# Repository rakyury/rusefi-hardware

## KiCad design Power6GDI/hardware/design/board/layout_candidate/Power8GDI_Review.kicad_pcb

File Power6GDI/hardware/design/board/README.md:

# Review PCB builder

**Incomplete engineering PCB. Do not fabricate, energize or claim qualification.**
The original placeholder PCB is untouched. This folder builds real footprints,
pad nets and routed subdomains from the current electrical hierarchy.

Use the pinned official `kicad/kicad:9.0` image, KiCad9.0.9; digest is recorded
in `source_provenance.json`. No network is needed during generation. Mount the
repository at`/src`, set working directory`/src`, and run:

```text
python3 Power6GDI/hardware/design/board/build_connector_schematic.py
kicad-cli sch export netlist --format kicadxml -o Power6GDI/hardware/design/board/connectors.xml Power6GDI/hardware/design/board/connectors.kicad_sch
python3 Power6GDI/hardware/design/board/build_board.py
python3 Power6GDI/hardware/design/board/verify_board.py Power6GDI/hardware/design/board/review/Power8GDI_Review.kicad_pcb Power6GDI/hardware/design/core.net
kicad-cli pcb drc --format json --all-track-errors --severity-all --exit-code-violations -o Power6GDI/hardware/design/board/review/drc.json Power6GDI/hardware/design/board/review/Power8GDI_Review.kicad_pcb
```

The authoritative integrated root XML is `design/core.net`. It includes
J601..604, so the current verifier uses only this XML. Duplicate refs
and conflicting pad assignments are errors. Before root integration the
builder also accepts whole separate GDI/power XML sheets; a partially duplicate
hierarchy is rejected. `--design-root`, `--source-board`, `--pinout` and
`--output-dir` support isolated build snapshots without editing source designs.

Source electrical flags includingDNP and BOM exclusion are carried to the
physical board and independently compared on reload. A source off-board
component fails instead of silently becoming a physical pad.

The copper transfer uses KiCad's actual source connectivity graph, exact
oldref→newref mapping and sourcepad→targetnet mapping. It rejects any source
net that would join two distinct target nets. Branches terminating at removed
logic/connectors and open physical endpoints are removed. Ground vias count
as real plane endpoints only with a retained pad. Groundplane fill and DRC are
run on the resulting board. Reference power/sense-zone shapes remain visible;
source clearances are **not** automatically accepted as new design rules.

The stageB reference3V3/5V supply buses cross the provisional edge when rotated;
they are explicitly omitted for rerouting to the new regulators. Remaining
unrouted connections are reported, not represented by invented tracks.

The provisional outline245×165mm,4-layer1.6mm stackup and clearances are design
inputs, not a manufacturer's approved stackup. Outer copper70µm, inner35µm,
dielectrics120/1130/120µm, soldermask10µm each side are an engineering proposal.
Current, thermal, impedance, transient, dielectric and assembly budgets remain
open. PCB pads/trace exports alone do not demonstrate electrical qualification.

The outline, donor stage frames, connector/MCU/ignition anchors and functional
regions come from `layout_profiles/<name>.json` (`--layout-profile`, default
`layout_profiles/245x165.json`). `compare_boards.py A B` proves two builds are
geometrically identical. `ground_stitch.py <board>` adds guarded GND vias for
islands on a saved, filled candidate (one per island; refused where copper,
holes, mask or the edge leave no room). See `docs/PCB_LAYOUT_PROFILE_2026_11_05.md`.
`review_autoroute.py <placement> <autorouted> <out>` measures the machine copper
of an autorouted candidate block by block (layers incl. In1, widths against the
project netclasses, the project clearance rule on every router item, sensitive
nets near switching copper, diff pairs, GND islands, remaining gap per block);
verdicts are written by hand in `docs/PCB_AUTOROUTE_REVIEW_2026_11_10.md`.

Run portable contract tests with:

```text
python -m unittest discover -s Power6GDI/hardware/design/board/tests -v
```

`render_preview.py` optionally converts actual KiCad SVG plots toPNG using
PyQt6/QtSvg. It does not infer or invent copper. Rendered exports and full DRC
reports belong in the chosen build/output directory; no manufacturing Gerber
release is produced while the DRC and functional gates fail.

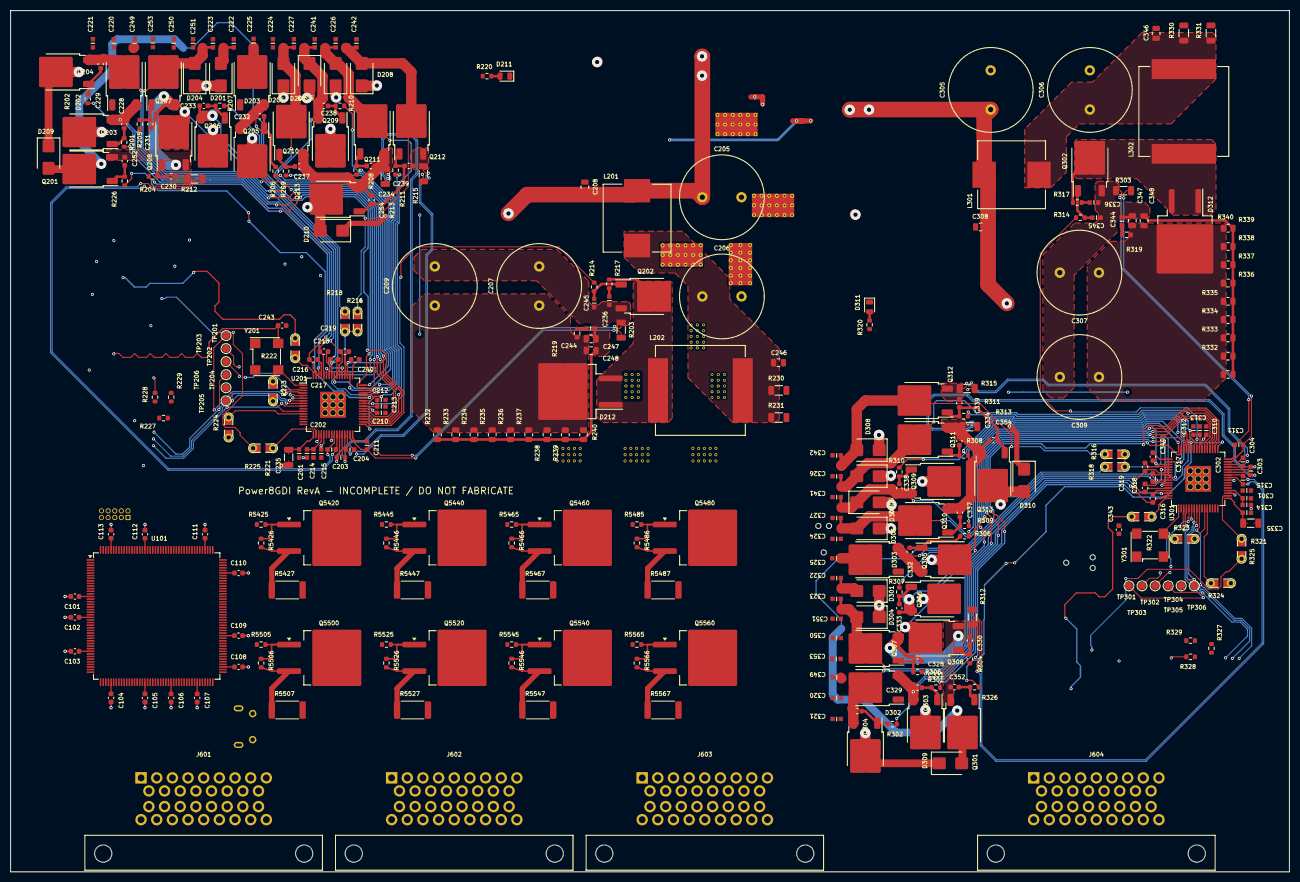
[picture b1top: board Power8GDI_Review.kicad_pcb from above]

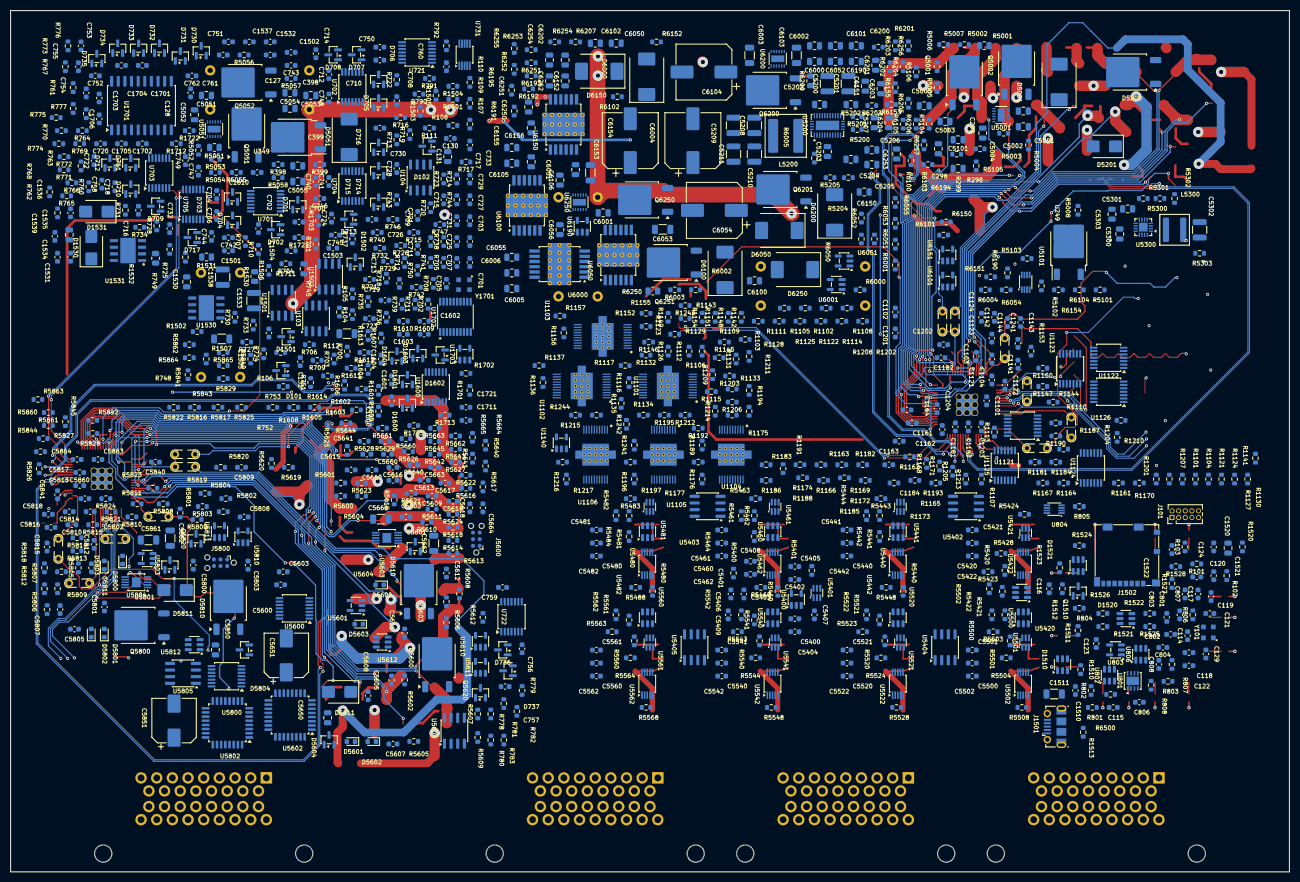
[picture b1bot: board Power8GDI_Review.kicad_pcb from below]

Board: 4 copper layers, 245.0 x 165.0 mm, 1262 parts (954 on the bottom side), 760 nets.

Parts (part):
C101, C102, C103, C104, C105, C106, C107, C108, C109, C110, C111, C112, C113, C117, C119, C121, C123, C124, C127, C128, C740, C742, C744, C746, C748, C758, C759, C761, C1101, C1102, C1103, C1121, C1122, C1123, C1141, C1142, C1143, C1161, C1162, C1163, C1181, C1182, C1183, C1201, C1202, C1203, C1241, C1501, C1502, C1510, C1520, C1532, C1537, C1610, C5640, C5641, C5660, C5663, C5664, C5840, C5841, C5860, C5863, C5864: 100n 16V X7R; C_0603_1608Metric
C114: 4.7u 16V X7R; C_0603_1608Metric
C115, C116: 2.2u 10V X7R; C_0603_1608Metric
C118, C120, C122, C741, C743, C745, C747, C749, C762, C1104, C1124, C1144, C1164, C1184, C1204: 1u 16V X7R; C_0603_1608Metric
C129, C701, C703, C705, C707, C709, C711, C713, C715, C717, C719, C721, C723, C725, C727, C729, C731, C733: 10n 16V X7R; C_0603_1608Metric
C130, C1503, C1531, C1534, C1536, C1539: 100n 50V X7R; C_0603_1608Metric
C131, C1504, C1530, C1535: 1u 50V X7R; C_0805_2012Metric
C132, C760, C1505: 1n 100V C0G; C_0603_1608Metric
C201, C301: 1u; REF_C9
C202, C302: 330p; REF_C10
C203, C303: 330p; REF_C11
C204, C304: 330p; REF_C13
C205, C305: 1200uF; REF_C14
C206, C306: 1200uF; REF_C15
C207, C307: 470uF; REF_C16
C208, C308: 0.22uF; REF_C17
C209, C309: 470uF; REF_C21
C210, C310: 100n; REF_C23
C211, C311: 330p; REF_C24
C212, C312: 4.7u; REF_C26
C213, C313: 100n; REF_C28
C214, C314: 100n; REF_C32
C215, C315: 100n; REF_C34
C216, C316: 0.33uF; REF_C39
C217, C317: 0.33uF; REF_C40
C218, C318: 0.33uF; REF_C41
C219, C319: 0.33uF; REF_C42
C220, C320: 4700p; REF_C43
C221, C321: 4700p; REF_C44
C222, C322: 4700p; REF_C45
C223, C323: 4700p; REF_C46
C224, C324: 4700p; REF_C47
C225, C325: 4700p; REF_C48
C226, C326: 4700p; REF_C49
C227, C327: 4700p; REF_C50
C228, C328: 1000pF; REF_C52
C229, C329: 1000pF; REF_C53
C230, C330: 1000pF; REF_C54
C231, C331: 1000pF; REF_C55
C232, C332: 1000pF; REF_C56
C233, C333: 1000pF; REF_C57
C234, C334: 1000pF; REF_C58
C235, C335: 100n; REF_C59
C236, C336: 330p; REF_C60
C237, C337: 1000pF; REF_C61
C238, C338: 1000pF; REF_C62
C239, C339: 1000pF; REF_C63
C240, C340: 0.33uF; REF_C64
C241, C341: 4700p; REF_C65
C242, C342: 4700p; REF_C67
C243, C343: 1000pF; REF_C71
C244, C344: 330p; REF_C73
C245, C345: 470p; REF_C74
C246, C346: 0.22uF; REF_C80
C247, C347: 0.22uF; REF_C81
C248, C348: 0.22uF; REF_C82
C249, C349: 4700p; REF_C84
C250, C350: 4700p; REF_C85
C251, C351: 4700p; REF_C86
C252, C352: 1000pF; REF_C87
C253, C353: 4700p; REF_C88
C254, C354: 1000pF; REF_C89
C298, C398: 330n 50V X7R; REF_C17
C299, C399: 100n 25V X7R; REF_C17
C700, C702, C704, C706, C708, C710, C712, C714, C716, C718, C720, C722, C724, C726, C728, C730, C732: 1n 50V C0G; C_0603_1608Metric
C750, C751, C752, C753, C754, C755, C756, C757, C1600, C1601, C1602, C1603, C1604: 47p 100V C0G; C_0603_1608Metric
C801, C802, C803, C804, C807, C1702, C1703, C1704, C1705, C1706: 100nF 25V X7R; C_0603_1608Metric
C806: 120pF 50V C0G 1%; C_0603_1608Metric
C808: 1nF 50V C0G 5%; C_0603_1608Metric
C1511: 1n 2kV C0G; C_1206_3216Metric
C1521: 10u 16V X7R; C_0805_2012Metric
C1522: 1n 16V X7R; C_0603_1608Metric
C1533, C1538: 22u 50V X7R; C_1210_3225Metric
C1701: 4.7uF 16V X7R; C_0603_1608Metric
C1711, C1721: 3.3nF 50V C0G; C_0603_1608Metric
C5001, C5003, C5051, C5053, C5650, C5850, C6200, C6202, C6250, C6252: 100n 100V X7R; C_0805_2012Metric
C5002, C5052, C5101, C5301, C6000, C6001, C6050, C6051, C6100, C6101, C6150, C6151, C6190, C6201, C6251: 100n 25V X7R; C_0805_2012Metric
C5004, C5054, C6002, C6052, C6102, C6152, C6203, C6253: 100n 50V X7R; C_0805_2012Metric
C5005, C5055, C6204, C6254: 22n 100V X7R; C_0805_2012Metric
C5200, C5201: 10u 100V X7R; C_1210_3225Metric
C5202: 47n 100V X7R; C_0805_2012Metric
C5203: 470n 25V X7R; C_0805_2012Metric
C5204: 2.2u 16V X7R; C_0805_2012Metric
C5205: 1u 16V X7R; C_0805_2012Metric
C5206: 22n 16V X7R; C_0805_2012Metric
C5207: 180p 50V C0G; C_0805_2012Metric
C5208, C5209, C5210, C5211: 47u 25V X7R; C_1210_3225Metric
C5300: 10u 25V X7R; C_0805_2012Metric
C5302: 22u 16V X7R; C_1210_3225Metric
C5303: 3.3n 25V C0G; C_0805_2012Metric
C5400, C5401, C5402, C5404, C5406, C5408, C5420, C5421, C5422, C5440, C5441, C5442, C5460, C5461, C5462, C5480, C5481, C5482, C5500, C5501, C5502, C5520, C5521, C5522, C5540, C5541, C5542, C5560, C5561, C5562: 100n 25V X7R; C_0603_1608Metric
C5403, C5405, C5407, C5409: 1u 25V X7R; C_0603_1608Metric
C5600, C5607, C5609, C5610, C5611, C5800, C5807, C5809, C5810, C5811: 1u; C_0603_1608Metric
C5601, C5602, C5605, C5608, C5612, C5613, C5614, C5615, C5617, C5618, C5801, C5802, C5805, C5808, C5812, C5813, C5814, C5815, C5817, C5818: 100n; C_0603_1608Metric
C5603, C5803: 33n; C_0603_1608Metric
C5616, C5816: 4.7u; C_0603_1608Metric
C5651, C5851: 47u 63V lowESR; CP_Elec_8x10
C5661, C5662, C5861, C5862: 10u 16V X7R effective>=4.7u; C_1206_3216Metric
C6003, C6053, C6103, C6153: 1u 50V X7R; C_1206_3216Metric
C6004, C6054, C6104, C6154: 100u 50V low ESR; CP_Elec_10x10.5
C6005, C6006, C6055, C6056, C6105, C6106, C6155, C6156: 1n 100V C0G; C_0805_2012Metric
D101, D1501: PESD2CAN; SOT-23
D102, D1502: BAS21,215; SOT-23
D201, D301: STPS2H100UY; REF_D9
D202, D302: SBR10200CTL; REF_D10
D203, D303: SBR10200CTL; REF_D11
D204, D304: STPS2H100UY; REF_D12
D205, D305: STPS2H100UY; REF_D13
D206, D306: STPS2H100UY; REF_D14
D207, D307: STPS2H100UY; REF_D15
D208, D308: STPS2H100UY; REF_D16
D209, D309: STPS2H100UY; REF_D17
D210, D310: STPS2H100UY; REF_D19
D211, D311: LED_Small; REF_D31
D212, D312: SDURB1020CT; REF_D34
D701, D702, D703, D704, D705, D706, D707, D708, D709, D710, D711, D712, D713, D714, D715, D716, D717, D730, D731, D732, D733, D734, D735, D736, D737, D1600, D1601, D1602, D1603, D1604: BAT54S,215; SOT-23
D1510, D1520, D1521: USBLC6-2SC6; SOT-23-6
D1530, D1531: STPS2H100UY; D_SMB
D5001, D5051, D6200, D6250: SMCJ33CA; D_SMC
D5200, D5610, D5810: STPS5H100BY-TR; TO-252-2
D5201, D5611, D5811: SMBJ24CA; D_SMB
D5600, D5603, D5800, D5803: LED-RED-0603; LED_0603_1608Metric
D5601, D5801: LED-GREEN-0603; LED_0603_1608Metric
D5602, D5802: LED-BLUE-0603; LED_0603_1608Metric
D5604, D5804: PESD1CAN; SOT-23
D6000, D6050, D6100, D6150: SMCJ18CA; D_SMC
J101: SWD 3V3 target reference; PinHeader_2x05_P1.27mm_Vertical
J601, J602, J603, J604: 6437288-1 / KEY1 CANDIDATE; TE_6437288-1_34way
J1501: Molex 1050170001; USB_Micro-B_Molex-105017-0001
J1502: Molex 1040310811; microSD_HC_Molex_104031-0811
J5600, J5800: Conn_02x03_Odd_Even; Tag-Connect_TC2030-IDC-NL_2x03_P1.27mm_Vertical
L201, L301: 6.8uH; REF_L1
L202, L302: 10uH; REF_L2
L5200: XAL7070-682MEC 6.8uH; L_Coilcraft_XAL7070-XXX
L5300: XAL5030-222MEC 2.2uH; L_Coilcraft_XAL5030-XXX
Q201, Q301: BUK9230-100B; REF_Q1
Q202, Q302: BUK9230-100B; REF_Q2
Q203, Q303: BUK9230-100B; REF_Q3
Q204, Q304: BUK9230-100B; REF_Q4
Q205, Q305: BUK9230-100B; REF_Q5
Q206, Q306: BUK9230-100B; REF_Q6
Q207, Q307: BUK9230-100B; REF_Q7
Q208, Q308: BUK9230-100B; REF_Q8
Q209, Q309: BUK9230-100B; REF_Q9
Q210, Q310: BUK9230-100B; REF_Q10
Q211, Q311: BUK9230-100B; REF_Q11
Q212, Q312: BUK9230-100B; REF_Q12
Q213, Q313: BUK9230-100B; REF_Q16
Q1510: 2N7002,215; SOT-23
Q5001, Q5002, Q5051, Q5052, Q6200, Q6201, Q6250, Q6251: IPD90N10S4-06; TO-252-2
Q5420, Q5440, Q5460, Q5480, Q5500, Q5520, Q5540, Q5560: STGB18N40LZT4; TO-263-2
Q5600, Q5800: VND7NV04TR-E; TO-252-2
Q5620, Q5820: BC847B-QR; SOT-23
R101, R111, R1506, R1520, R1713, R1723, R5644, R5844, R6500: 0R; R_0603_1608Metric
R102, R103, R104, R108, R110, R760, R763, R766, R769, R772, R775, R778, R781, R792, R1103, R1106, R1109, R1112, R1114, R1117, R1123, R1126, R1129, R1132, R1134, R1137, R1143, R1146, R1149, R1152, R1154, R1157, R1163, R1166, R1169, R1172, R1174, R1177, R1183, R1186, R1189, R1192, R1194, R1197, R1203, R1206, R1209, R1212, R1214, R1217, R1501, R1504, R1505, R1512, R1600, R1603, R1606, R1609, R1612, R5426, R5446, R5466, R5486, R5506, R5526, R5546, R5566, R5604, R5605, R5613, R5614, R5618, R5619, R5625, R5640, R5641, R5643, R5662, R5804, R5805, R5813, R5814, R5818, R5819, R5825, R5840, R5841, R5843, R5862, R6002, R6003, R6004, R6005, R6052, R6053, R6054, R6055, R6102, R6103, R6104, R6105, R6152, R6153, R6154, R6155, R6193, R6194, R6203, R6207, R6253, R6257: 10k; R_0603_1608Metric
R105, R109, R1513: 0R DNP; R_0603_1608Metric
R106, R1502, R5629, R5829: 120R DNP; R_0603_1608Metric
R107, R1503: 4.7k; R_0603_1608Metric
R112, R1507: 1k 1% 0.5W; R_1206_3216Metric
R201, R301: 10; REF_R10
R202, R302: 10; REF_R11
R203, R303: 0.01; REF_R12
R204, R304: 10; REF_R13
R205, R305: 10; REF_R14
R206, R306: 10; REF_R15
R207, R307: 10; REF_R16
R208, R308: 10; REF_R17
R209, R309: 10; REF_R18
R210, R310: 10; REF_R19
R211, R311: 10; REF_R20
R212, R312: 0.01; REF_R21
R213, R313: 0.01; REF_R22
R214, R314: 10; REF_R24
R215, R315: 0.01; REF_R26
R216, R316: Jumper-Pad-Pad; REF_R37
R217, R317: 220; REF_R38
R218, R318: DNP; REF_R41
R219, R319: 5.1; REF_R42
R220, R320: 75K; REF_R43
R221, R321: 0.01; REF_R45
R222, R322: DNP; REF_R80
R223, R323: DNP; REF_R81
R224, R324: DNP; REF_R82
R225, R325: DNP; REF_R83
R226, R326: 10; REF_R94
R227, R327: 1K; REF_R123
R228, R328: 1K; REF_R124
R229, R329: 1K; REF_R125
R230, R330: 2K; REF_R126
R231, R331: 2K; REF_R127
R232, R332: 56k; REF_R128
R233, R333: 56k; REF_R129
R234, R334: 56k; REF_R130
R235, R335: 56k; REF_R131
R236, R336: 56k; REF_R132
R237, R337: 56k; REF_R133
R238, R338: 56k; REF_R134
R239, R339: 56k; REF_R135
R240, R340: 56k; REF_R136
R298, R398: 910 1% minimum load; REF_R123
R299, R399: DNP_ENABLE_BOUNDARY; REF_R123
R700, R701, R703, R704, R706, R707, R709, R710, R712, R713, R715, R716, R718, R719, R721, R722, R724, R725, R727, R728, R730, R731, R733, R734, R736, R737, R739, R740, R742, R743, R745, R746, R748, R749, R5200, R5203, R5300: 100k 0.1%; R_0603_1608Metric
R702, R705, R708, R711, R714, R717, R720, R723, R726, R729, R732, R735, R738, R741, R744, R747, R750, R1510, R5401, R5600, R5601, R5616, R5617, R5622, R5626, R5627, R5628, R5800, R5801, R5816, R5817, R5822, R5826, R5827, R5828, R6202, R6206, R6252, R6256: 1k; R_0603_1608Metric
R751, R752, R753: 2.49k DNP; R_0603_1608Metric
R761, R764, R767, R770, R773, R776, R779, R782, R1523, R1524, R1525, R1526, R1527, R1528, R1601, R1604, R1607, R1610, R1613: 47k; R_0603_1608Metric
R762, R765, R768, R771, R774, R777, R780, R783, R1602, R1605, R1608, R1611, R1614: 10k DNP; R_0603_1608Metric
R790, R791, R5002, R5052, R6201, R6251: 10k 0.1%; R_0603_1608Metric
R801, R802, R803, R804, R805, R806, R1701, R1702, R5004, R5008, R5054, R5058, R5101, R5102, R5103, R5104, R5105, R5106, R5303, R5400, R5665, R5865: 10k 1%; R_0603_1608Metric
R807: 102k 0.1% 25ppm; R_0603_1608Metric
R808: 9.76k 0.1% 25ppm; R_0603_1608Metric
R1101, R1104, R1107, R1110, R1121, R1124, R1127, R1130, R1141, R1144, R1147, R1150, R1161, R1164, R1167, R1170, R1181, R1184, R1187, R1190, R1201, R1204, R1207, R1210, R1241, R1511, R5420, R5424, R5440, R5444, R5460, R5464, R5480, R5484, R5500, R5504, R5520, R5524, R5540, R5544, R5560, R5564, R5615, R5621, R5645, R5815, R5821, R5845, R6195: 100k; R_0603_1608Metric
R1102, R1105, R1108, R1111, R1115, R1116, R1122, R1125, R1128, R1131, R1135, R1136, R1142, R1145, R1148, R1151, R1155, R1156, R1162, R1165, R1168, R1171, R1175, R1176, R1182, R1185, R1188, R1191, R1195, R1196, R1202, R1205, R1208, R1211, R1215, R1216, R6000, R6001, R6050, R6051, R6100, R6101, R6150, R6151: 100R; R_0603_1608Metric
R1113, R1133, R1153, R1173, R1193, R1213, R6190, R6191, R6192: 47R; R_0603_1608Metric
R1242, R5003, R5007, R5053, R5057: 1k 1%; R_0603_1608Metric
R1243, R1244: 33R; R_0603_1608Metric
R1521, R1522: 22R; R_0603_1608Metric
R1530, R1531, R1532: 0R star return; R_0805_2012Metric
R1703, R1711, R1712, R1721, R1722, R5204, R5302, R5422, R5442, R5462, R5482, R5502, R5522, R5542, R5562: 100k 1%; R_0603_1608Metric
R5001, R5051, R6200, R6250: 140k 0.1%; R_0805_2012Metric
R5005, R5006, R5055, R5056, R5205: 1M 1%; R_0603_1608Metric
R5201: 25k 0.1%; R_0603_1608Metric
R5202: 470k 0.1%; R_0805_2012Metric
R5301: 32k 0.1%; R_0603_1608Metric
R5421, R5441, R5461, R5481, R5501, R5521, R5541, R5561: 147k 1% 25ppm; R_0603_1608Metric
R5423, R5443, R5463, R5483, R5503, R5523, R5543, R5563: 39.2k 1%; R_0603_1608Metric
R5425, R5445, R5465, R5485, R5505, R5525, R5545, R5565: 10R; R_0603_1608Metric
R5427, R5447, R5467, R5487, R5507, R5527, R5547, R5567: WSLP2512R0100FEA; R_2512_6332Metric
R5428, R5448, R5468, R5488, R5508, R5528, R5548, R5568: 4.99k 1% 25ppm; R_0603_1608Metric
R5602, R5603, R5802, R5803: 68k; R_0603_1608Metric
R5606, R5806: 10; R_0603_1608Metric
R5607, R5807: 22k; R_0603_1608Metric
R5608, R5808: 47; R_0603_1608Metric
R5609, R5809: 61.9; R_0603_1608Metric
R5610, R5611, R5612, R5810, R5811, R5812: 20k; R_0603_1608Metric
R5620, R5623, R5820, R5823: 27k; R_0603_1608Metric
R5624, R5824: 3.3k; R_0603_1608Metric
R5642, R5661, R5842, R5861: 2.2k 1%; R_0603_1608Metric
R5660, R5860: 30k 0.1%; R_0603_1608Metric
R5663, R5863: 220R 0.1%; R_0603_1608Metric
R5664, R5864: 4.7k 1%; R_0603_1608Metric
R6204, R6205, R6254, R6255: 1M; R_0603_1608Metric
TP201, TP301: TestPoint; REF_S1
TP202, TP302: TestPoint; REF_S2
TP203, TP303: TestPoint; REF_S3
TP204, TP304: TestPoint; REF_S4
TP205, TP305: TestPoint; REF_S5
TP206, TP306: TestPoint; REF_S6
U101: STM32F767IIT6; LQFP-176_24x24mm_P0.5mm
U103, U1501: TCAN1042HGVDRQ1; SOIC-8_3.9x4.9mm_P1.27mm
U104, U1502: TLIN1029ADRQ1; SOIC-8_3.9x4.9mm_P1.27mm
U201, U301: MC33PT2001AE; REF_U1
U249, U349: NCV78M05ABDTRKG; REF_U3
U701, U702, U703, U704, U705: TLV9004QPWRQ1; TSSOP-14_4.4x5mm_P0.65mm
U721, U722, U1121, U1122, U1123, U1124, U1125, U1126, U1600: SN74LVC14AQPWRQ1; TSSOP-14_4.4x5mm_P0.65mm
U731: MAX9924UAUB/V+; MSOP-10_3x3mm_P0.5mm
U801: TPS3431SQDRBRQ1; VSON-8-1EP_3x3mm_P0.65mm_EP1.6x2.4mm
U802, U5612, U5812: TPS3808G33QDBVRQ1; SOT-23-6
U803, U1140, U5400: SN74LVC1G17QDBVRQ1; SOT-23-5
U804: SN74LVC2G74QDCURQ1; VSSOP-8_2.3x2mm_P0.5mm
U806: TPS3808G01QDBVRQ1; SOT-23-6
U1101, U1102, U1103, U1104, U1105, U1106: TLE9104SHXUMA1; TLE9104SH_PG-DSO-20-88
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
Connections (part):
+3V3: C101.1, C102.1, C103.1, C104.1, C105.1, C106.1, C107.1, C108.1, C109.1, C110.1, C111.1, C112.1, C113.1, C114.1, C119.1, C120.1, C121.1, C122.1, C123.1, C128.1, C129.1, C243.2, C343.2, C758.1, C759.1, C801.1, C802.1, C803.1, C804.1, C807.1, C1101.1, C1102.1, C1121.1, C1122.1, C1141.1, C1142.1, C1161.1, C1162.1, C1181.1, C1182.1, C1201.1, C1202.1, C1241.1, C1502.1, C1610.1, C1705.1, C1706.1, C5101.1, C5302.1, C5400.1, C5401.1, C5420.1, C5421.1, C5422.1, C5440.1, C5441.1, C5442.1, C5460.1, C5461.1, C5462.1, C5480.1, C5481.1, C5482.1, C5500.1, C5501.1, C5502.1, C5520.1, C5521.1, C5522.1, C5540.1, C5541.1, C5542.1, C5560.1, C5561.1, C5562.1, C6000.1, C6001.1, C6050.1, C6051.1, C6100.1, C6101.1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
+3V3_A: C117.1, C118.1, C740.1, C741.1, C742.1, C743.1, C744.1, C745.1, C746.1, C747.1, C748.1, C749.1, D701.2, D702.2, D703.2, D704.2, D705.2, D706.2, D707.2, D708.2, D709.2, D710.2, D711.2, D712.2, D713.2, D714.2, D715.2, D716.2, D717.2, R101.2, U101.38, U101.39, U701.4, U702.4, U703.4, U704.4, U705.4
+5V_CORE: C127.1, C761.1, C762.1, C1103.1, C1104.1, C1123.1, C1124.1, C1143.1, C1144.1, C1163.1, C1164.1, C1183.1, C1184.1, C1203.1, C1204.1, C1501.1, C1532.1, C1537.1, C1701.1, C1702.1, C1704.1, C5205.1, C5207.1, C5208.1, C5209.1, C5210.1, C5211.1, C5300.1, C5301.1, C5402.1, C5403.1, C5404.1, C5405.1, C5406.1, C5407.1, C5408.1, C5409.1, C5610.1, C5613.1, C5617.1, C5641.1, C5661.1, C5810.1, C5813.1, C5817.1, C5841.1, C5861.1, D730.2, D731.2, D732.2, D733.2, D734.2, D735.2, D736.2, D737.2, D1600.2, D1601.2, D1602.2, D1603.2, D1604.2, L5200.2, R751.1, R752.1, R753.1, R762.1, R765.1, R768.1, R771.1, R774.1, R777.1, R780.1, R783.1, R807.1, R1602.1, R1605.1, R1608.1, R1611.1, R1614.1, R5200.1, R5204.1, R5642.2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
+5V_GDI_A: C215.2, C299.1, R298.1, U201.21 (VCC5), U249.3
+5V_GDI_B: C315.2, C399.1, R398.1, U301.21 (VCC5), U349.3
ADC_AUX_ANALOG1: C731.1, R747.2, U101.28
ADC_AUX_ANALOG2: C733.1, R750.2, U101.26
ADC_BARO_EXT: C711.1, R717.2, U101.52
ADC_CLT: C713.1, R720.2, U101.53
ADC_EWG_POS: C729.1, R744.2, U101.24
ADC_EXH_PRESS: C727.1, R741.2, U101.55
ADC_FRP1: C721.1, R732.2, U101.34
ADC_FRP2: C723.1, R735.2, U101.35
ADC_IAT: C715.1, R723.2, U101.56
ADC_LPFP_PRESS: C725.1, R738.2, U101.54
ADC_MAP_MAIN: C709.1, R714.2, U101.51
ADC_OIL_PRESS: C717.1, R726.2, U101.32
ADC_OIL_TEMP: C719.1, R729.2, U101.33
ADC_PPS1: C705.1, R708.2, U101.47
ADC_PPS2: C707.1, R711.2, U101.50
ADC_TPS1: C701.1, R702.2, U101.40
ADC_TPS2: C703.1, R705.2, U101.42
ADC_UNUSED_18: U705.6, U705.7
ADC_UNUSED_19: U705.8, U705.9
ADC_UNUSED_20: U705.13, U705.14
AUX_ANALOG1_BUFFER: R747.1, U704.13, U704.14
AUX_ANALOG1_DIV: C730.1, D716.3, R745.2, R746.1, U704.12
AUX_ANALOG2_BUFFER: R750.1, U705.1, U705.2
AUX_ANALOG2_DIV: C732.1, D717.3, R748.2, R749.1, U705.3
AUX_PWM1: R1161.1, U101.67, U1124.1
AUX_PWM1_INV: R1162.1, U1124.2
AUX_PWM1_IN_N: R1162.2, R1163.2, U1104.3
AUX_PWM2: R1164.1, U101.106, U1124.3
AUX_PWM2_INV: R1165.1, U1124.4
AUX_PWM2_IN_N: R1165.2, R1166.2, U1104.18
AUX_PWM3: R1167.1, U101.107, U1124.5
AUX_PWM3_INV: R1168.1, U1124.6
AUX_PWM3_IN_N: R1168.2, R1169.2, U1104.4
AUX_PWM4: R1170.1, U101.108, U1124.9
AUX_PWM4_INV: R1171.1, U1124.8
AUX_PWM4_IN_N: R1171.2, R1172.2, U1104.17
AUX_PWM5: R1181.1, U101.109, U1125.1
AUX_PWM5_INV: R1182.1, U1125.2
AUX_PWM5_IN_N: R1182.2, R1183.2, U1105.3
AUX_PWM6: R1184.1, U101.110, U1125.3
AUX_PWM6_INV: R1185.1, U1125.4
AUX_PWM6_IN_N: R1185.2, R1186.2, U1105.18
AUX_PWM7: R1187.1, U101.157, U1125.5
AUX_PWM7_INV: R1188.1, U1125.6
AUX_PWM7_IN_N: R1188.2, R1189.2, U1105.4
AUX_PWM8: R1190.1, U101.160, U1125.9
AUX_PWM8_INV: R1191.1, U1125.8
AUX_PWM8_IN_N: R1191.2, R1192.2, U1105.17
AUX_SPI_MOSI_5V: U1701.12, U1702.18
AUX_SPI_SCK_5V: U1701.13, U1702.16
BARO_EXT_BUFFER: R717.1, U702.6, U702.7
BARO_EXT_DIV: C710.1, D706.3, R715.2, R716.1, U702.5
BOOT0: R103.1, U101.166
CAM1: U101.19, U721.2
CAM1_FILTERED: C750.1, D730.3, R760.2, R761.1, U721.1
CAM2: U101.20, U721.4
CAM2_FILTERED: C751.1, D731.3, R763.2, R764.1, U721.3
CAM3: U101.174, U721.6
CAM3_FILTERED: C752.1, D732.3, R766.2, R767.1, U721.5
CAM4: U101.175, U721.8
CAM4_FILTERED: C753.1, D733.3, R769.2, R770.1, U721.9
CAN1_H: D101.1, J604.11, R106.1, U103.7
CAN1_L: D101.2, J604.12, R106.2, U103.6
CAN1_RX: U101.142, U103.4
CAN1_STB: R104.2, R105.1, U101.43, U103.8
CAN1_TX: U101.143, U103.1
CAN2_H: D1501.1, D5604.1, D5804.1, J604.13, R1502.1, R5629.2, R5829.2, U1501.7, U5605.7, U5805.7
CAN2_L: D1501.2, D5604.2, D5804.2, J604.14, R1502.2, R5629.1, R5829.1, U1501.6, U5605.6, U5805.6
CAN2_RX: U101.163, U1501.4
CAN2_STB: R1501.2, U101.155, U1501.8
CAN2_TX: U101.164, U1501.1
CLT_BUFFER: R720.1, U702.8, U702.9
CLT_DIV: C712.1, D707.3, R718.2, R719.1, U702.10
CRANK: R792.2, U101.57, U731.7
DBW_DIR: R6001.1, U101.133
DBW_DIR_FILTERED: R6001.2, R6003.1, U6000.1
DBW_DISABLE: R6004.1, U101.101, U6001.2
DBW_DIS_GATED: R6005.1, U6000.11, U6001.4
DBW_MOTOR_A: C6005.1, J604.1, U6000.5
DBW_MOTOR_B: C6006.1, J604.2, U6000.7
DBW_PWM: R6000.1, U101.115
DBW_PWM_FILTERED: R6000.2, R6002.1, U6000.12
DBW_SPI_SO: U6000.3, U6050.8
DI1: TP201.1, U101.111, U201.4 (START1)
DI2: TP202.1, U101.112, U201.5 (START2)
DI3: TP203.1, U101.99, U201.6 (START3)
DI4: TP204.1, U101.98, U201.7 (START4)
DI5: TP301.1, U101.97, U301.4 (START1)
DI6: TP302.1, U101.60, U301.5 (START2)
DI7: TP303.1, U101.63, U301.6 (START3)
DI8: TP304.1, U101.64, U301.7 (START4)
EWG_DIR: R6051.1, U101.104
EWG_DIR_FILTERED: R6051.2, R6053.1, U6050.1
EWG_DISABLE: R6054.1, U101.105, U6051.2
EWG_DIS_GATED: R6055.1, U6050.11, U6051.4
EWG_MOTOR_A: C6055.1, J604.3, U6050.5
EWG_MOTOR_B: C6056.1, J604.4, U6050.7
EWG_POS_BUFFER: R744.1, U704.8, U704.9
EWG_POS_DIV: C728.1, D715.3, R742.2, R743.1, U704.10
EWG_PWM: R6050.1, U101.117
EWG_PWM_FILTERED: R6050.2, R6052.1, U6050.12
EWG_SPI_SO: U6050.3, U6100.8
EXH_PRESS_BUFFER: R741.1, U704.6, U704.7
EXH_PRESS_DIV: C726.1, D714.3, R739.2, R740.1, U704.5
FLEX_FREQ: U101.7, U1600.10
FLEX_FREQ_FILTERED: C1604.1, D1604.3, R1612.2, R1613.1, U1600.11
FRP1_BUFFER: R732.1, U703.8, U703.9
FRP1_DIV: C720.1, D711.3, R730.2, R731.1, U703.10
FRP2_BUFFER: R735.1, U703.13, U703.14
FRP2_DIV: C722.1, D712.3, R733.2, R734.1, U703.12
GDI_A_CAP: C5002.1, U5001.11
GDI_A_DGATE: Q5001.1, R5005.1, U5001.1
GDI_A_HGATE: Q5002.1, R5006.1, R5007.1, U5001.8
GDI_A_MID: C5001.1, C5002.2, Q5001.2, Q5002.2, U5001.10, U5001.12
GDI_A_OV: R5001.2, R5002.1, U5001.5
GDI_A_POWER_EN: R5003.2, R5004.1, U5001.6
GDI_A_SLEW: C5005.1, R5007.2
GDI_A_SW: R5001.1, U5001.4
GDI_B_CAP: C5052.1, U5051.11
GDI_B_DGATE: Q5051.1, R5055.1, U5051.1
GDI_B_HGATE: Q5052.1, R5056.1, R5057.1, U5051.8
GDI_B_MID: C5051.1, C5052.2, Q5051.2, Q5052.2, U5051.10, U5051.12
GDI_B_OV: R5051.2, R5052.1, U5051.5
GDI_B_POWER_EN: R5053.2, R5054.1, U5051.6
GDI_B_SLEW: C5055.1, R5057.2
GDI_B_SW: R5051.1, U5051.4
GDI_SPI2_MISO: R1115.2, R1135.2, R1155.2, R1175.2, R1195.2, R1215.2, R6192.2, U101.94, U201.15 (MISO), U301.15 (MISO), U1703.4
GDI_SPI2_MOSI: R1244.1, R6190.1, U101.95, U201.14 (MOSI), U301.14 (MOSI), U1702.2
GDI_SPI2_SCK: R1243.1, R6191.1, U101.93, U201.16 (SCK), U301.16 (SCK), U1702.4
GND: C101.2, C102.2, C103.2, C104.2, C105.2, C106.2, C107.2, C108.2, C109.2, C110.2, C111.2, C112.2, C113.2, C114.2, C115.2, C116.2, C117.2, C118.2, C119.2, C120.2, C121.2, C122.2, C123.2, C124.2, C127.2, C128.2, C129.2, C130.2, C131.2, C132.2, C201.1, C205.2, C206.2, C208.2, C210.1, C212.1, C213.1, C214.1, C215.1, C220.1, C221.1, C222.1, C223.1, C224.1, C225.1, C226.1, C227.1, C235.1, C241.1, C242.1, C243.1, C246.2, C249.1, C250.1, C251.1, C253.1, C298.2, C299.2, C301.1, C305.2, C306.2, C308.2, C310.1, C312.1, C313.1, C314.1, C315.1, C320.1, C321.1, C322.1, C323.1, C324.1, C325.1, C326.1, C327.1, C335.1, C341.1, C342.1, C343.1, C346.2, C349.1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
HALL1: U101.129, U1600.2
HALL1_FILTERED: C1600.1, D1600.3, R1600.2, R1601.1, U1600.1
HALL2: U101.130, U1600.4
HALL2_FILTERED: C1601.1, D1601.3, R1603.2, R1604.1, U1600.3
HALL3: U101.131, U1600.6
HALL3_FILTERED: C1602.1, D1602.3, R1606.2, R1607.1, U1600.5
HALL4: U101.176, U1600.8
HALL4_FILTERED: C1603.1, D1603.3, R1609.2, R1610.1, U1600.9
HARNESS_AUX_ANALOG1: J604.19, R745.1
HARNESS_AUX_ANALOG2: J604.20, R748.1
HARNESS_AUX_PWM1: J602.21, U1104.1
HARNESS_AUX_PWM2: J602.22, U1104.20
HARNESS_AUX_PWM3: J602.23, U1104.10
HARNESS_AUX_PWM4: J602.24, U1104.11
HARNESS_AUX_PWM5: J602.25, U1105.1
HARNESS_AUX_PWM6: J602.26, U1105.20
HARNESS_AUX_PWM7: J602.27, U1105.10
HARNESS_AUX_PWM8: J602.28, U1105.11
HARNESS_BARO_EXT: J603.20, R715.1
HARNESS_CAM1: J603.3, R760.1, R762.2
HARNESS_CAM2: J603.4, R763.1, R765.2
HARNESS_CAM3: J603.5, R766.1, R768.2
HARNESS_CAM4: J603.6, R769.1, R771.2
HARNESS_CLT: J603.21, R718.1, R751.2
HARNESS_CRANK_VR_N: J603.2, R791.1
HARNESS_CRANK_VR_P: J603.1, R790.1
HARNESS_EWG_POS: J603.29, R742.1
HARNESS_EXH_PRESS: J603.28, R739.1
HARNESS_FLEX_FREQ: J603.30, R1612.1, R1614.2
HARNESS_FRP1: J603.25, R730.1
HARNESS_FRP2: J603.26, R733.1
HARNESS_HALL1: J603.7, R1600.1, R1602.2
HARNESS_HALL2: J603.8, R1603.1, R1605.2
HARNESS_HALL3: J603.9, R1606.1, R1608.2
HARNESS_HALL4: J603.10, R1609.1, R1611.2
HARNESS_IAT: J603.22, R721.1, R752.2
HARNESS_IGN1: J602.1, Q5420.2
HARNESS_IGN2: J602.2, Q5440.2
HARNESS_IGN3: J602.3, Q5460.2
HARNESS_IGN4: J602.4, Q5480.2
HARNESS_IGN5: J602.5, Q5500.2
HARNESS_IGN6: J602.6, Q5520.2
HARNESS_IGN7: J602.7, Q5540.2
HARNESS_IGN8: J602.8, Q5560.2
HARNESS_KNOCK1_RETURN: J603.12, R1713.1
HARNESS_KNOCK1_SIG: C1711.1, J603.11
HARNESS_KNOCK2_RETURN: J603.14, R1723.1
HARNESS_KNOCK2_SIG: C1721.1, J603.13
HARNESS_LPFP_PRESS: J603.27, R736.1
HARNESS_LS_AUX1: J602.29, U1106.1
HARNESS_LS_AUX2: J602.30, U1106.20
HARNESS_LS_AUX3: J602.31, U1106.10
HARNESS_LS_AUX4: J602.32, U1106.11
HARNESS_MAP_MAIN: J603.19, R712.1
HARNESS_OIL_PRESS: J603.23, R724.1
HARNESS_OIL_TEMP: J603.24, R727.1, R753.2
HARNESS_PI1: J602.9, U1101.1
HARNESS_PI2: J602.10, U1101.20
HARNESS_PI3: J602.11, U1101.10
HARNESS_PI4: J602.12, U1101.11
HARNESS_PI5: J602.13, U1102.1
HARNESS_PI6: J602.14, U1102.20
HARNESS_PI7: J602.15, U1102.10
HARNESS_PI8: J602.16, U1102.11
HARNESS_PPS1: J603.17, R706.1
HARNESS_PPS2: J603.18, R709.1
HARNESS_SENSOR_GND_A: J603.33, R1530.1
HARNESS_SENSOR_GND_B: J603.34, R1531.1
HARNESS_SENSOR_GND_C: J604.34, R1532.1
HARNESS_SENT1: J604.5, R772.1, R774.2
HARNESS_SENT2: J604.6, R775.1, R777.2
HARNESS_SENT3: J604.7, R778.1, R780.2
HARNESS_SENT4: J604.8, R781.1, R783.2
HARNESS_TPS1: J603.15, R700.1
HARNESS_TPS2: J603.16, R703.1
HARNESS_VVT1: J602.17, U1103.1
HARNESS_VVT2: J602.18, U1103.20
HARNESS_VVT3: J602.19, U1103.10
HARNESS_VVT4: J602.20, U1103.11
HARNESS_WBO1_CONTACT1: J604.21, R5609.2, R5614.2
HARNESS_WBO1_CONTACT2: C5607.1, J604.22, R5606.1, R5618.1, U5602.7
HARNESS_WBO1_CONTACT3: J604.23, Q5600.2
HARNESS_WBO1_CONTACT4: C5650.1, C5651.1, D5610.2, D5611.1, J604.24
HARNESS_WBO1_CONTACT5: J604.25, R5605.1, R5608.1, R5609.1, R5613.2
HARNESS_WBO1_CONTACT6: C5605.1, J604.26, R5612.1, U5600.10
HARNESS_WBO2_CONTACT1: J604.27, R5809.2, R5814.2
HARNESS_WBO2_CONTACT2: C5807.1, J604.28, R5806.1, R5818.1, U5802.7
HARNESS_WBO2_CONTACT3: J604.29, Q5800.2
HARNESS_WBO2_CONTACT4: C5850.1, C5851.1, D5810.2, D5811.1, J604.30
HARNESS_WBO2_CONTACT5: J604.31, R5805.1, R5808.1, R5809.1, R5813.2
HARNESS_WBO2_CONTACT6: C5805.1, J604.32, R5812.1, U5800.10
HPFP1: TP206.1, U101.96, U201.9 (START6)
HPFP2: TP306.1, U101.100, U301.9 (START6)
HW_ACTUATOR_ENABLE: R806.1, R1116.1, R1136.1, R1156.1, R1176.1, R1196.1, R1216.1, R5003.1, R5053.1, R5664.1, R5864.1, R6202.1, R6252.1, U804.5, U5101.2, U5101.6, U5401.1
HW_ACTUATOR_ENABLE_N: R805.1, R6194.1, U804.3, U6001.1, U6051.1, U6101.1, U6151.1
HW_KILL_N: R802.1, R6500.2, U802.3
IAT_BUFFER: R723.1, U702.13, U702.14
IAT_DIV: C714.1, D708.3, R721.2, R722.1, U702.12
IGN1: R5420.1, U101.8, U5420.1, U5421.1
IGN1_DIV: R5422.2, R5423.1, U5420.4
IGN1_DRIVE: R5425.1, U5402.7
IGN1_GATE: Q5420.1, R5425.2, R5426.1
IGN1_GUARDED: R5424.1, U5402.2, U5421.4
IGN1_ILIMIT: R5428.1, U5422.3
IGN1_SET: R5421.1, U5420.3
IGN1_SHUNT_HI: Q5420.3, R5426.2, R5427.1, U5422.1
IGN1_WINDOW: U5420.6, U5421.3
IGN2: R5440.1, U101.4, U5440.1, U5441.1
IGN2_DIV: R5442.2, R5443.1, U5440.4
IGN2_DRIVE: R5445.1, U5402.5
IGN2_GATE: Q5440.1, R5445.2, R5446.1
IGN2_GUARDED: R5444.1, U5402.4, U5441.4
IGN2_ILIMIT: R5448.1, U5442.3
IGN2_SET: R5441.1, U5440.3
IGN2_SHUNT_HI: Q5440.3, R5446.2, R5447.1, U5442.1
IGN2_WINDOW: U5440.6, U5441.3
IGN3: R5460.1, U101.3, U5460.1, U5461.1
IGN3_DIV: R5462.2, R5463.1, U5460.4
IGN3_DRIVE: R5465.1, U5403.7
IGN3_GATE: Q5460.1, R5465.2, R5466.1
IGN3_GUARDED: R5464.1, U5403.2, U5461.4
IGN3_ILIMIT: R5468.1, U5462.3
IGN3_SET: R5461.1, U5460.3
IGN3_SHUNT_HI: Q5460.3, R5466.2, R5467.1, U5462.1
IGN3_WINDOW: U5460.6, U5461.3
IGN4: R5480.1, U101.2, U5480.1, U5481.1
IGN4_DIV: R5482.2, R5483.1, U5480.4
IGN4_DRIVE: R5485.1, U5403.5
IGN4_GATE: Q5480.1, R5485.2, R5486.1
IGN4_GUARDED: R5484.1, U5403.4, U5481.4
IGN4_ILIMIT: R5488.1, U5482.3
IGN4_SET: R5481.1, U5480.3
IGN4_SHUNT_HI: Q5480.3, R5486.2, R5487.1, U5482.1
IGN4_WINDOW: U5480.6, U5481.3
IGN5: R5500.1, U101.1, U5500.1, U5501.1
IGN5_DIV: R5502.2, R5503.1, U5500.4
IGN5_DRIVE: R5505.1, U5404.7
IGN5_GATE: Q5500.1, R5505.2, R5506.1
IGN5_GUARDED: R5504.1, U5404.2, U5501.4
IGN5_ILIMIT: R5508.1, U5502.3
IGN5_SET: R5501.1, U5500.3
IGN5_SHUNT_HI: Q5500.3, R5506.2, R5507.1, U5502.1
IGN5_WINDOW: U5500.6, U5501.3
IGN6: R5520.1, U101.167, U5520.1, U5521.1
IGN6_DIV: R5522.2, R5523.1, U5520.4
IGN6_DRIVE: R5525.1, U5404.5
IGN6_GATE: Q5520.1, R5525.2, R5526.1
IGN6_GUARDED: R5524.1, U5404.4, U5521.4
IGN6_ILIMIT: R5528.1, U5522.3
IGN6_SET: R5521.1, U5520.3
IGN6_SHUNT_HI: Q5520.3, R5526.2, R5527.1, U5522.1
IGN6_WINDOW: U5520.6, U5521.3
IGN7: R5540.1, U101.168, U5540.1, U5541.1
IGN7_DIV: R5542.2, R5543.1, U5540.4
IGN7_DRIVE: R5545.1, U5405.7
IGN7_GATE: Q5540.1, R5545.2, R5546.1
IGN7_GUARDED: R5544.1, U5405.2, U5541.4
IGN7_ILIMIT: R5548.1, U5542.3
IGN7_SET: R5541.1, U5540.3
IGN7_SHUNT_HI: Q5540.3, R5546.2, R5547.1, U5542.1
IGN7_WINDOW: U5540.6, U5541.3
IGN8: R5560.1, U101.5, U5560.1, U5561.1
IGN8_DIV: R5562.2, R5563.1, U5560.4
IGN8_DRIVE: R5565.1, U5405.5
IGN8_GATE: Q5560.1, R5565.2, R5566.1
IGN8_GUARDED: R5564.1, U5405.4, U5561.4
IGN8_ILIMIT: R5568.1, U5562.3
IGN8_SET: R5561.1, U5560.3
IGN8_SHUNT_HI: Q5560.3, R5566.2, R5567.1, U5562.1
IGN8_WINDOW: U5560.6, U5561.3
IGN_OC_OK: R5400.2, R6500.1, U5400.2, U5422.5, U5442.5, U5462.5, U5482.5, U5502.5, U5522.5, U5542.5, U5562.5
IGN_OC_OK_CLEAN: U5400.4, U5401.3
IGN_SAFE_EN: R5401.1, U5401.4, U5402.1, U5402.8, U5403.1, U5403.8, U5404.1, U5404.8, U5405.1, U5405.8, U5421.6, U5441.6, U5461.6, U5481.6, U5501.6, U5521.6, U5541.6, U5561.6
KNOCK1_AC: C1711.2, R1711.1
KNOCK1_FB: R1712.1, U1701.18
KNOCK1_INV: R1711.2, R1712.2, U1701.19
KNOCK2_AC: C1721.2, R1721.1
KNOCK2_FB: R1722.1, U1701.17
KNOCK2_INV: R1721.2, R1722.2, U1701.16
KNOCK_CLK_5V: U1701.9, U1702.9
KNOCK_CS_N: R1701.1, U101.132, U1702.6, U1703.1
KNOCK_CS_N_5V: U1701.8, U1702.14
KNOCK_INT_HOLD: R1702.1, U101.11, U1702.8
KNOCK_INT_HOLD_5V: U1701.7, U1702.12
KNOCK_OSC_3V3: U1702.11, Y1701.3
KNOCK_SDO_5V: R1703.1, U1701.11, U1703.2
KNOCK_VREF: C1703.1, U1701.3, U1701.15, U1701.20
LIN1_BUS: C132.1, J604.9, R112.2, U104.6
LIN1_COMMANDER_DIODE: D102.3, R112.1
LIN1_EN: R108.1, R109.2, U101.44, U104.2
LIN1_RX: R107.2, U101.150, U104.1
LIN1_TX: R110.2, U101.147, U104.4
LIN1_VSUP: C130.1, C131.1, D102.1, R111.2, U104.7
LIN2_BUS: C1505.1, J604.10, R1507.2, U1502.6
LIN2_COMMANDER_DIODE: D1502.3, R1507.1
LIN2_EN: R1504.1, U101.156, U1502.2
LIN2_RX: R1503.2, U101.80, U1502.1
LIN2_TX: R1505.2, U101.79, U1502.4
LIN2_VSUP: C1503.1, C1504.1, D1502.1, R1506.2, U1502.7
LP5_BOOT: C5203.1, U5200.6
LP5_EN: R5202.2, R5203.1, U5200.18
LP5_FB: C5207.2, R5200.2, R5201.1, U5200.12
LP5_PG_RAW: R5204.2, R5205.1, U5200.16, U5300.13
LP5_SS: C5206.1, U5200.11
LP5_SW: C5203.2, L5200.1, U5200.1, U5200.2, U5200.3, U5200.4, U5200.5
LP5_VCC: C5204.1, U5200.8
LP33_FB: R5300.2, R5301.1, U5300.5
LP33_SS: C5303.1, U5300.9
LP33_SW: L5300.1, U5300.1, U5300.2, U5300.3
LPFP_PRESS_BUFFER: R738.1, U704.1, U704.2
LPFP_PRESS_DIV: C724.1, D713.3, R736.2, R737.1, U704.3
LS1_CS_N: R1113.2, R1114.2, U1101.7
LS1_ENABLE: R1116.2, R1117.1, U1101.14
LS1_SO: R1115.1, U1101.5
LS2_CS_N: R1133.2, R1134.2, U1102.7
LS2_ENABLE: R1136.2, R1137.1, U1102.14
LS2_SO: R1135.1, U1102.5
LS3_CS_N: R1153.2, R1154.2, U1103.7
LS3_ENABLE: R1156.2, R1157.1, U1103.14
LS3_SO: R1155.1, U1103.5
LS4_CS_N: R1173.2, R1174.2, U1104.7
LS4_ENABLE: R1176.2, R1177.1, U1104.14
LS4_SO: R1175.1, U1104.5
LS5_CS_N: R1193.2, R1194.2, U1105.7
LS5_ENABLE: R1196.2, R1197.1, U1105.14
LS5_SO: R1195.1, U1105.5
LS6_CS_N: R1213.2, R1214.2, U1106.7
LS6_ENABLE: R1216.2, R1217.1, U1106.14
LS6_SO: R1215.1, U1106.5
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
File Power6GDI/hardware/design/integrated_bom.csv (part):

Reference,Value,Footprint,DNP,Assembly_Class,Quantity_Per_Board,SMT_Placement_Quantity,Exclude_From_BOM,Reference_MPN,MPN_Status,Procurement_Status,Orderable_MPN,Manufacturer,Selection_ID,Selection_Status,Hardware_Qualification,Selection_Gaps,Selection_Ratings,Selection_Source_URLs,Purchase_Released,Sheet,Datasheet,Source_LCSC,Source_Fields_JSON,Source_Netlist_SHA256
C101,100n 16V X7R,Capacitor_SMD:C_0603_1608Metric,False,SURFACE_MOUNT,1,1,False,C0603C104K5RACTU,EXPLICIT_FIELD_CANDIDATE,NOT_PURCHASE_QUALIFIED,C0603C104K5RACTU,KEMET,SEL-6bf9727c4e40,SELECTED_CATALOG_ITEM,BOARD_QUALIFICATION_PENDING,[],"{""capacitance_pf"": 100000, ""dielectric"": ""X7R"", ""rated_voltage_v"": 50, ""temperature_max_c"": 125, ""temperature_min_c"": -55, ""tolerance_pct"": 10}",https://search.kemet.com/download/specsheet/C0603C104K5RACTU,False,"/MCU, power decoupling and debug/",,,"{""Datasheet"": """", ""Description"": """", ""Design note"": ""Place directly at U101 VDD pad 15; short GND return"", ""Footprint"": ""Capacitor_SMD:C_0603_1608Metric"", ""Hardware_Qualification"": ""BOARD_QUALIFICATION_PENDING"", ""MPN"": ""C0603C104K5RACTU"", ""Manufacturer"": ""KEMET"", ""Procurement_Status"": ""SELECTED_CATALOG_ITEM"", ""Purchase_Released"": ""false"", ""Selection_Gaps"": ""[]"", ""Selection_ID"": ""SEL-6bf9727c4e40"", ""Selection_Ratings"": ""{\""capacitance_pf\"": 100000, \""dielectric\"": \""X7R\"", \""rated_voltage_v\"": 50, \""temperature_max_c\"": 125, \""temperature_min_c\"": -55, \""tolerance_pct\"": 10}"", ""Selection_Source_URLs"": ""https://search.kemet.com/download/specsheet/C0603C104K5RACTU""}",abd9c0533019b9811a75fa73c46c1a9d9b97511d5f858edb2b88ae1e98a87462
C102,100n 16V X7R,Capacitor_SMD:C_0603_1608Metric,False,SURFACE_MOUNT,1,1,False,C0603C104K5RACTU,EXPLICIT_FIELD_CANDIDATE,NOT_PURCHASE_QUALIFIED,C0603C104K5RACTU,KEMET,SEL-6bf9727c4e40,SELECTED_CATALOG_ITEM,BOARD_QUALIFICATION_PENDING,[],"{""capacitance_pf"": 100000, ""dielectric"": ""X7R"", ""rated_voltage_v"": 50, ""temperature_max_c"": 125, ""temperature_min_c"": -55, ""tolerance_pct"": 10}",https://search.kemet.com/download/specsheet/C0603C104K5RACTU,False,"/MCU, power decoupling and debug/",,,"{""Datasheet"": """", ""Description"": """", ""Design note"": ""Place directly at U101 VDD pad 23; short GND return"", ""Footprint"": ""Capacitor_SMD:C_0603_1608Metric"", ""Hardware_Qualification"": ""BOARD_QUALIFICATION_PENDING"", ""MPN"": ""C0603C104K5RACTU"", ""Manufacturer"": ""KEMET"", ""Procurement_Status"": ""SELECTED_CATALOG_ITEM"", ""Purchase_Released"": ""false"", ""Selection_Gaps"": ""[]"", ""Selection_ID"": ""SEL-6bf9727c4e40"", ""Selection_Ratings"": ""{\""capacitance_pf\"": 100000, \""dielectric\"": \""X7R\"", \""rated_voltage_v\"": 50, \""temperature_max_c\"": 125, \""temperature_min_c\"": -55, \""tolerance_pct\"": 10}"", ""Selection_Source_URLs"": ""https://search.kemet.com/download/specsheet/C0603C104K5RACTU""}",abd9c0533019b9811a75fa73c46c1a9d9b97511d5f858edb2b88ae1e98a87462
C103,100n 16V X7R,Capacitor_SMD:C_0603_1608Metric,False,SURFACE_MOUNT,1,1,False,C0603C104K5RACTU,EXPLICIT_FIELD_CANDIDATE,NOT_PURCHASE_QUALIFIED,C0603C104K5RACTU,KEMET,SEL-6bf9727c4e40,SELECTED_CATALOG_ITEM,BOARD_QUALIFICATION_PENDING,[],"{""capacitance_pf"": 100000, ""dielectric"": ""X7R"", ""rated_voltage_v"": 50, ""temperature_max_c"": 125, ""temperature_min_c"": -55, ""tolerance_pct"": 10}",https://search.kemet.com/download/specsheet/C0603C104K5RACTU,False,"/MCU, power decoupling and debug/",,,"{""Datasheet"": """", ""Description"": """", ""Design note"": ""Place directly at U101 VDD pad 36; short GND return"", ""Footprint"": ""Capacitor_SMD:C_0603_1608Metric"", ""Hardware_Qualification"": ""BOARD_QUALIFICATION_PENDING"", ""MPN"": ""C0603C104K5RACTU"", ""Manufacturer"": ""KEMET"", ""Procurement_Status"": ""SELECTED_CATALOG_ITEM"", ""Purchase_Released"": ""false"", ""Selection_Gaps"": ""[]"", ""Selection_ID"": ""SEL-6bf9727c4e40"", ""Selection_Ratings"": ""{\""capacitance_pf\"": 100000, \""dielectric\"": \""X7R\"", \""rated_voltage_v\"": 50, \""temperature_max_c\"": 125, \""temperature_min_c\"": -55, \""tolerance_pct\"": 10}"", ""Selection_Source_URLs"": ""https://search.kemet.com/download/specsheet/C0603C104K5RACTU""}",abd9c0533019b9811a75fa73c46c1a9d9b97511d5f858edb2b88ae1e98a87462
C104,100n 16V X7R,Capacitor_SMD:C_0603_1608Metric,False,SURFACE_MOUNT,1,1,False,C0603C104K5RACTU,EXPLICIT_FIELD_CANDIDATE,NOT_PURCHASE_QUALIFIED,C0603C104K5RACTU,KEMET,SEL-6bf9727c4e40,SELECTED_CATALOG_ITEM,BOARD_QUALIFICATION_PENDING,[],"{""capacitance_pf"": 100000, ""dielectric"": ""X7R"", ""rated_voltage_v"": 50, ""temperature_max_c"": 125, ""temperature_min_c"": -55, ""tolerance_pct"": 10}",https://search.kemet.com/download/specsheet/C0603C104K5RACTU,False,"/MCU, power decoupling and debug/",,,"{""Datasheet"": """", ""Description"": """", ""Design note"": ""Place directly at U101 VDD pad 49; short GND return"", ""Footprint"": ""Capacitor_SMD:C_0603_1608Metric"", ""Hardware_Qualification"": ""BOARD_QUALIFICATION_PENDING"", ""MPN"": ""C0603C104K5RACTU"", ""Manufacturer"": ""KEMET"", ""Procurement_Status"": ""SELECTED_CATALOG_ITEM"", ""Purchase_Released"": ""false"", ""Selection_Gaps"": ""[]"", ""Selection_ID"": ""SEL-6bf9727c4e40"", ""Selection_Ratings"": ""{\""capacitance_pf\"": 100000, \""dielectric\"": \""X7R\"", \""rated_voltage_v\"": 50, \""temperature_max_c\"": 125, \""temperature_min_c\"": -55, \""tolerance_pct\"": 10}"", ""Selection_Source_URLs"": ""https://search.kemet.com/download/specsheet/C0603C104K5RACTU""}",abd9c0533019b9811a75fa73c46c1a9d9b97511d5f858edb2b88ae1e98a87462
C105,100n 16V X7R,Capacitor_SMD:C_0603_1608Metric,False,SURFACE_MOUNT,1,1,False,C0603C104K5RACTU,EXPLICIT_FIELD_CANDIDATE,NOT_PURCHASE_QUALIFIED,C0603C104K5RACTU,KEMET,SEL-6bf9727c4e40,SELECTED_CATALOG_ITEM,BOARD_QUALIFICATION_PENDING,[],"{""capacitance_pf"": 100000, ""dielectric"": ""X7R"", ""rated_voltage_v"": 50, ""temperature_max_c"": 125, ""temperature_min_c"": -55, ""tolerance_pct"": 10}",https://search.kemet.com/download/specsheet/C0603C104K5RACTU,False,"/MCU, power decoupling and debug/",,,"{""Datasheet"": """", ""Description"": """", ""Design note"": ""Place directly at U101 VDD pad 62; short GND return"", ""Footprint"": ""Capacitor_SMD:C_0603_1608Metric"", ""Hardware_Qualification"": ""BOARD_QUALIFICATION_PENDING"", ""MPN"": ""C0603C104K5RACTU"", ""Manufacturer"": ""KEMET"", ""Procurement_Status"": ""SELECTED_CATALOG_ITEM"", ""Purchase_Released"": ""false"", ""Selection_Gaps"": ""[]"", ""Selection_ID"": ""SEL-6bf9727c4e40"", ""Selection_Ratings"": ""{\""capacitance_pf\"": 100000, \""dielectric\"": \""X7R\"", \""rated_voltage_v\"": 50, \""temperature_max_c\"": 125, \""temperature_min_c\"": -55, \""tolerance_pct\"": 10}"", ""Selection_Source_URLs"": ""https://search.kemet.com/download/specsheet/C0603C104K5RACTU""}",abd9c0533019b9811a75fa73c46c1a9d9b97511d5f858edb2b88ae1e98a87462
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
